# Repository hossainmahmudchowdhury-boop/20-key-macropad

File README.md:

# 20-key-macropad

I have designed a functional macropad design mostly for programming enthusiastics. This design contains 4x5 grid which contains 20 keycaps . Anyone can customize it according to their need . In PCB I have used Seeduino XIAO and for this you can customized the keys in AHK. A potentiometer is also added for operating the macropad with simple matrix design

## Hardware Used

##### Schematic 

#### 1.Seeduino XIAO (MCU)
#### 2.20 × Mechanical Switches
#### 3.20 × Diodes 
#### 4.I/O Expander (for additional key inputs)
#### 5.USB Interface

## Case Design _
As this project emphasizes short way to conduct any command , I made my own custom case in three parts ,
the base one and the top part contain 75mm width and 100mm . The hight of the total case is 32mm  .

### Top Case

### Middle Case

### Base Case 

### Key Cap

## Software
In this hardware design I use KiCad (Version 10.0) for PCB integration . For case design I have used Fusion . 

## BOM

| Item                                             | Quantity | Price          | Link |
|--------------------------------------------------|----------|----------------|------|
| SEEED XIAO RP2040 (THT)                          | 1        | $$7.25          | [Link](https://www.seeedstudio.com/XIAO-RP2040-v1-0-p-5026.html) |
| Outemu Silent Peach V3 Switch                              | 10      | $6.09          | [Link](https://www.aliexpress.com/item/1005006905361113.html) |
| SK6812-MINI-E (RGB LEDs)                         | 25      | $5.26         | [Link](https://www.aliexpress.com/item/1005005193716172.html) |
| 1N4148 Diode                                     | 100      | $1.20          | [Link](https://www.aliexpress.com/item/4000142272546.html) |
| SSD1306 OLED Display                             | 1        | $5.15           | [Link](https://www.aliexpress.com/item/1005008640132638.html) |
| YMDK Blank DSA 1u Keycap                         | 20       | $12.86          | [Link](https://www.aliexpress.com/item/32842379355.html) |
| 45mm Straight Side Potentiometer                 | 1        | 3.15$           | [Link](https://alishort.com/0HUxU) |
| EC 11 Encoder with Push Button Half Handle 20MM Shaft | 5 | $6.31 | [Link](https://www.aliexpress.com/item/1005005983134515.html) |
| M3 Heat Set Inserts | 30 | $6.13 | [Link](https://www.aliexpress.com/item/1005006071488810.html) |
| M3 Fasteners | 50 | $6.28 | [Link](https://www.aliexpress.com/item/1005011845940916.html) |
| Top Case                                         | 1        | Printing Legion |  |
| Bottom Case                                      | 1        | Printing Legion |  |
| Middle Case                                      |           |  Printing Legion |   |
| PCB | 3 | $11.02 | JLCPCB |

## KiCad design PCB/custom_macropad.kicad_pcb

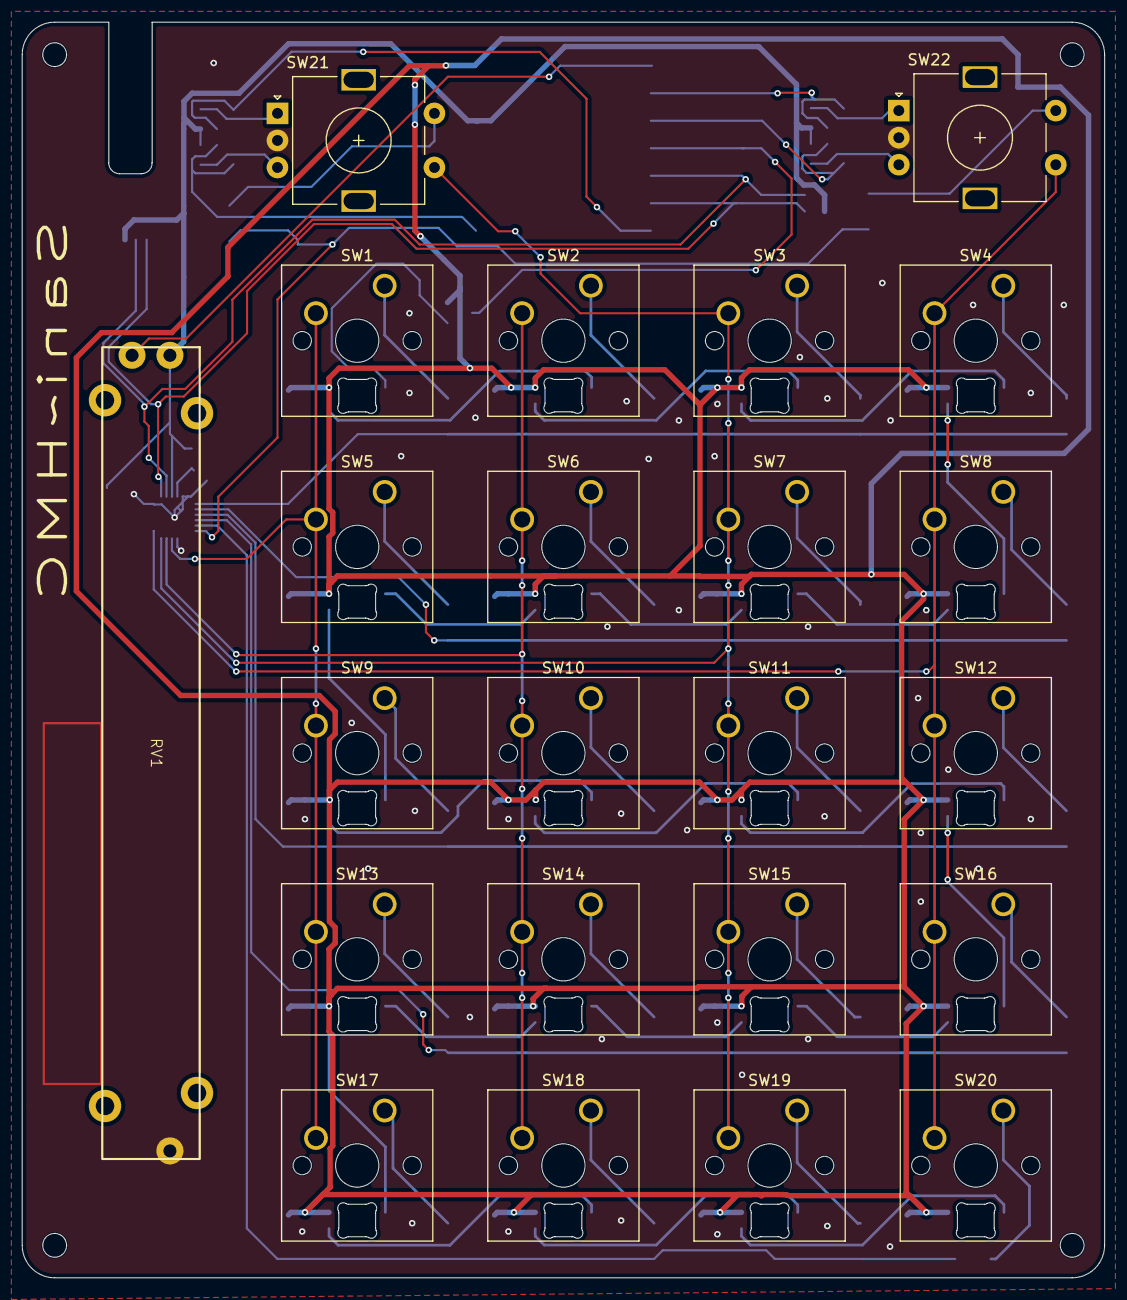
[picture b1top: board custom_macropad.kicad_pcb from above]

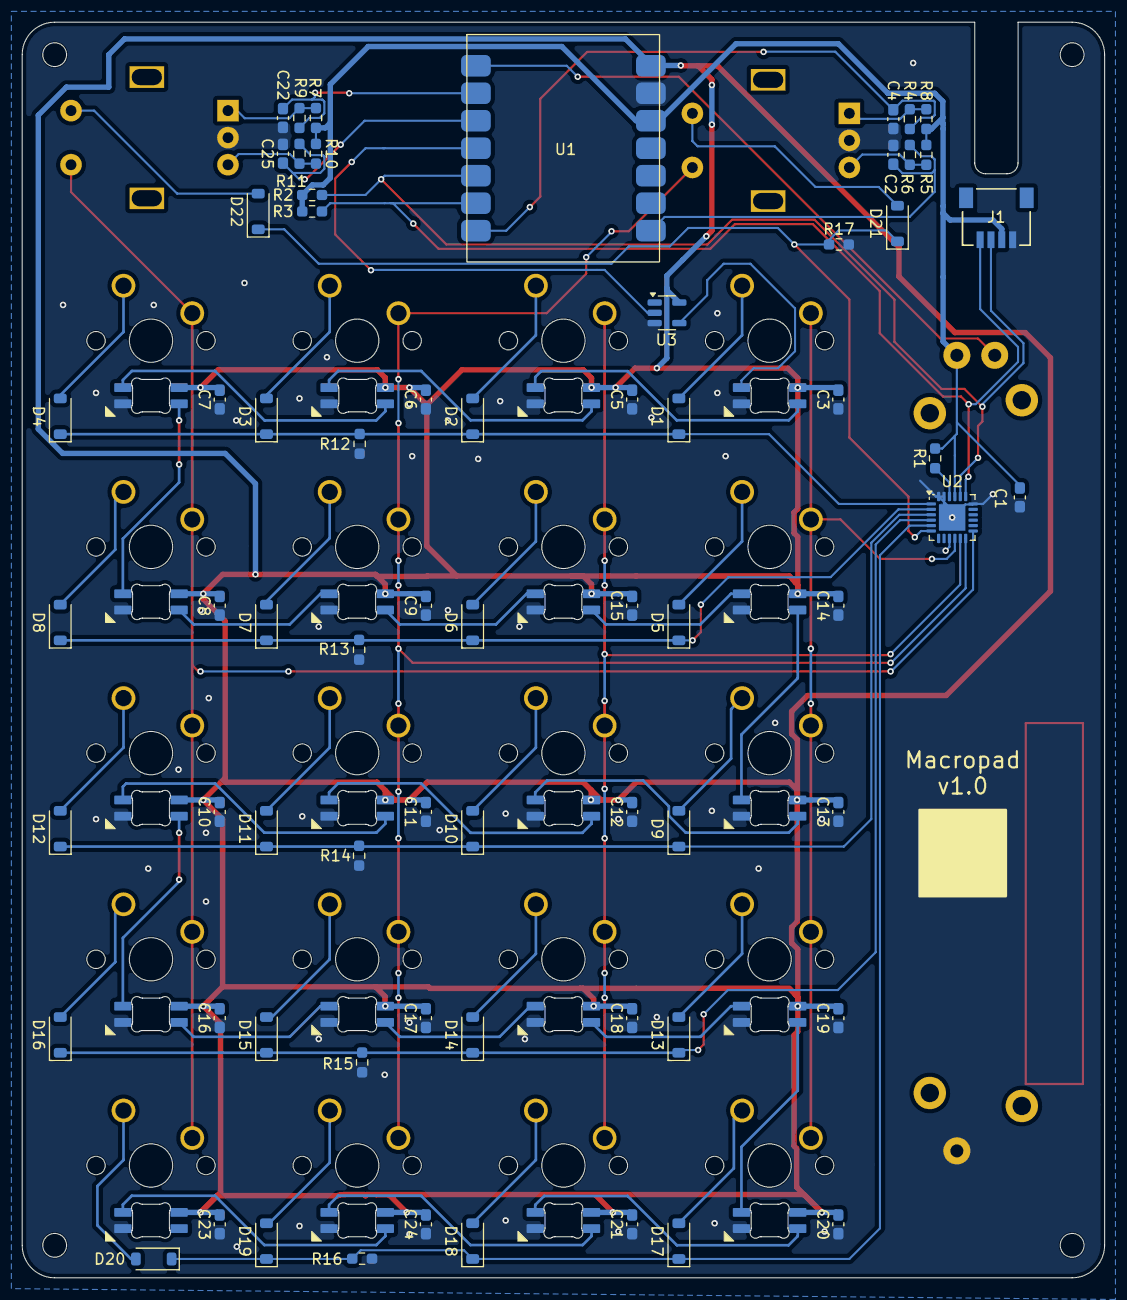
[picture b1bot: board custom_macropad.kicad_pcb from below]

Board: 2 copper layers, 100.0 x 116.0 mm, 115 parts (68 on the bottom side), 68 nets.

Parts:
C1, C3, C5, C6, C7, C8, C9, C10, C11, C12, C13, C14, C15, C16, C17, C18, C19, C20, C21, C23, C24: 0.1uF; C_0603_1608Metric_Pad1.08x0.95mm_HandSolder
C2, C4, C22, C25: 10nF; C_0603_1608Metric_Pad1.08x0.95mm_HandSolder
D1, D2, D3, D4, D5, D6, D7, D8, D9, D10, D11, D12, D13, D14, D15, D16, D17, D18, D19, D20, D21, D22: 1N4148W; D_SOD-123
H1, H2, H3, H4: MountingHole; MountingHole_2.2mm_M2
J1: SM04B-SRSS-TB; CONN_SM04B-SRSS-TB_JST
LED1, LED2, LED3, LED4, LED5, LED6, LED7, LED8, LED9, LED10, LED11, LED12, LED13, LED14, LED15, LED16, LED17, LED18, LED20, LED21: SK6812MINI-E; MX_SK6812MINI-E
R1, R2, R3: 4.7k; R_0603_1608Metric_Pad0.98x0.95mm_HandSolder
R4, R5, R6, R7, R8, R9, R10, R11, R12, R13, R14, R15, R16, R17: 10K; R_0603_1608Metric_Pad0.98x0.95mm_HandSolder
RV1: R_Potentiometer_US; PTA6043-2010CIB103
SW1, SW2, SW3, SW4, SW5, SW6, SW7, SW8, SW9, SW10, SW11, SW12, SW13, SW14, SW15, SW16, SW17, SW18, SW19, SW20: keyswitch; SW_Cherry_MX_1.00u_PCB
SW21, SW22: RotaryEncoder_Switch; RotaryEncoder_Alps_EC11E-Switch_Vertical_H20mm
U1: MOUDLE-SEEEDUINO-XIAO; MOUDLE14P-SMD-2.54-21X17.8MM
U2: TCA9555RTWR; WQFN-24-1EP_4x4mm_P0.5mm_EP2.45x2.45mm
U3: SN74LV1T34DBV; SOT-23-5

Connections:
+3V3: C1.1, J1.2, R1.2, R2.2, R3.2, R5.1, R8.1, R9.1, R10.1, RV1.1, U1.12 (3V3), U2.21 (VCC)
+5V: C3.2, C5.2, C6.2, C7.2, C8.2, C9.2, C10.2, C11.2, C12.2, C13.2, C14.2, C15.2, C16.2, C17.2, C18.2, C19.2, C20.2, C21.2, C23.2, C24.2, LED1.1 (VDD), LED2.1 (VDD), LED3.1 (VDD), LED4.1 (VDD), LED5.1 (VDD), LED6.1 (VDD), LED7.1 (VDD), LED8.1 (VDD), LED9.1 (VDD), LED10.1 (VDD), LED11.1 (VDD), LED12.1 (VDD), LED13.1 (VDD), LED14.1 (VDD), LED15.1 (VDD), LED16.1 (VDD), LED17.1 (VDD), LED18.1 (VDD), LED20.1 (VDD), LED21.1 (VDD), U1.14 (5V), U3.5 (VCC)
/COL1: SW1.2, SW5.2, SW9.2, SW13.2, SW17.2, U2.10
/COL2: SW2.2, SW6.2, SW10.2, SW14.2, SW18.2, U2.11
/COL3: SW3.2, SW7.2, SW11.2, SW15.2, SW19.2, SW21.S1, U2.12
/COL4: SW4.2, SW8.2, SW12.2, SW16.2, SW20.2, SW22.S1, U2.13
/ENC2_A: C22.2, R7.2, U1.2 (PA4_A1_D1)
/ENC2_B: C25.1, R11.1, U1.3 (PA10_A2_D2)
/ENC_A: C4.2, R4.2, U1.7 (PB08_A6_D6_TX)
/ENC_B: C2.1, R6.1, U1.8 (PB09_A7_D7_RX)
/LED: U1.4 (PA11_A3_D3), U3.2 (A)
/LED_5V: LED1.4 (DIN), U3.4 (Y)
/ROW1: D1.1 (K), D2.1 (K), D3.1 (K), D4.1 (K), R12.1, U2.1 (P00)
/ROW2: D5.1 (K), D6.1 (K), D7.1 (K), D8.1 (K), R13.1, U2.2 (P01)
/ROW3: D9.1 (K), D10.1 (K), D11.1 (K), D12.1 (K), R14.1, U2.3 (P02)
/ROW4: D13.1 (K), D14.1 (K), D15.1 (K), D16.1 (K), R15.1, U2.4 (P03)
/ROW5: D17.1 (K), D18.1 (K), D19.1 (K), D20.1 (K), R16.1, U2.5 (P04)
/ROW6: D21.1 (K), D22.1 (K), R17.1, U2.6 (P05)
/SCL: J1.4, R3.1, U1.6 (PA9_A5_D5_SCL), U2.19 (SCL)
/SDA: J1.3, R2.1, U1.5 (PA8_A4_D4_SDA), U2.20 (SDA)
/SLIDE: RV1.2, U1.1 (PA02_A0_D0)
//INT: R1.1, U2.22 (~INT)
GND: C1.2, C2.2, C3.1, C4.1, C5.1, C6.1, C7.1, C8.1, C9.1, C10.1, C11.1, C12.1, C13.1, C14.1, C15.1, C16.1, C17.1, C18.1, C19.1, C20.1, C21.1, C22.1, C23.1, C24.1, C25.2, J1.1, LED1.3 (VSS), LED2.3 (VSS), LED3.3 (VSS), LED4.3 (VSS), LED5.3 (VSS), LED6.3 (VSS), LED7.3 (VSS), LED8.3 (VSS), LED9.3 (VSS), LED10.3 (VSS), LED11.3 (VSS), LED12.3 (VSS), LED13.3 (VSS), LED14.3 (VSS), LED15.3 (VSS), LED16.3 (VSS), LED17.3 (VSS), LED18.3 (VSS), LED20.3 (VSS), LED21.3 (VSS), R12.2, R13.2, R14.2, R15.2, R16.2, R17.2, RV1.3, SW21.C, SW22.C, U1.13 (GND), U2.9 (GND), U2.18 (A0), U2.23 (A1), U2.24 (A2), U2.25 (EPAD), U3.3 (GND)
unnamed: D1.2 (A), SW1.1
unnamed: D2.2 (A), SW2.1
unnamed: D3.2 (A), SW3.1
unnamed: D4.2 (A), SW4.1
unnamed: D5.2 (A), SW5.1
unnamed: D6.2 (A), SW6.1
unnamed: D7.2 (A), SW7.1
unnamed: D8.2 (A), SW8.1
unnamed: D9.2 (A), SW9.1
unnamed: D10.2 (A), SW10.1
unnamed: D11.2 (A), SW11.1
unnamed: D12.2 (A), SW12.1
unnamed: D13.2 (A), SW13.1
unnamed: D14.2 (A), SW14.1
unnamed: D15.2 (A), SW15.1
unnamed: D16.2 (A), SW16.1
unnamed: D17.2 (A), SW17.1
unnamed: D18.2 (A), SW18.1
unnamed: D19.2 (A), SW19.1
unnamed: D20.2 (A), SW20.1
unnamed: D21.2 (A), SW21.S2
unnamed: D22.2 (A), SW22.S2
unnamed: LED1.2 (DOUT), LED2.4 (DIN)
unnamed: LED2.2 (DOUT), LED3.4 (DIN)
unnamed: LED3.2 (DOUT), LED4.4 (DIN)
unnamed: LED4.2 (DOUT), LED5.4 (DIN)
unnamed: LED5.2 (DOUT), LED6.4 (DIN)
unnamed: LED6.2 (DOUT), LED7.4 (DIN)
unnamed: LED7.2 (DOUT), LED8.4 (DIN)
unnamed: LED8.2 (DOUT), LED9.4 (DIN)
unnamed: LED9.2 (DOUT), LED10.4 (DIN)
unnamed: LED10.2 (DOUT), LED11.4 (DIN)
unnamed: LED11.2 (DOUT), LED12.4 (DIN)
unnamed: LED12.2 (DOUT), LED13.4 (DIN)
unnamed: LED13.2 (DOUT), LED14.4 (DIN)
unnamed: LED14.2 (DOUT), LED15.4 (DIN)
unnamed: LED15.2 (DOUT), LED16.4 (DIN)
unnamed: LED16.2 (DOUT), LED17.4 (DIN)
unnamed: LED17.2 (DOUT), LED18.4 (DIN)
unnamed: LED18.2 (DOUT), LED21.4 (DIN)
unnamed: LED20.4 (DIN), LED21.2 (DOUT)
unnamed: R4.1, R8.2, SW21.A
unnamed: R5.2, R6.2, SW21.B
unnamed: R7.1, R9.2, SW22.A
unnamed: R10.2, R11.2, SW22.B

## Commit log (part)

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2026-06-21 Update README.md
    Expanded README with features, hardware used, and project goal.
2026-06-21 Fix formatting and update features section in README
2026-06-21 Fix formatting and headers in README.md
    Updated formatting and corrected section headers in README.
2026-06-27 Adding hotkey script for desk and window management
    This script provides various hotkeys for controlling an adjustable desk, managing windows, switching HDMI inputs, and controlling USB devices, along with lighting and display power controls.
